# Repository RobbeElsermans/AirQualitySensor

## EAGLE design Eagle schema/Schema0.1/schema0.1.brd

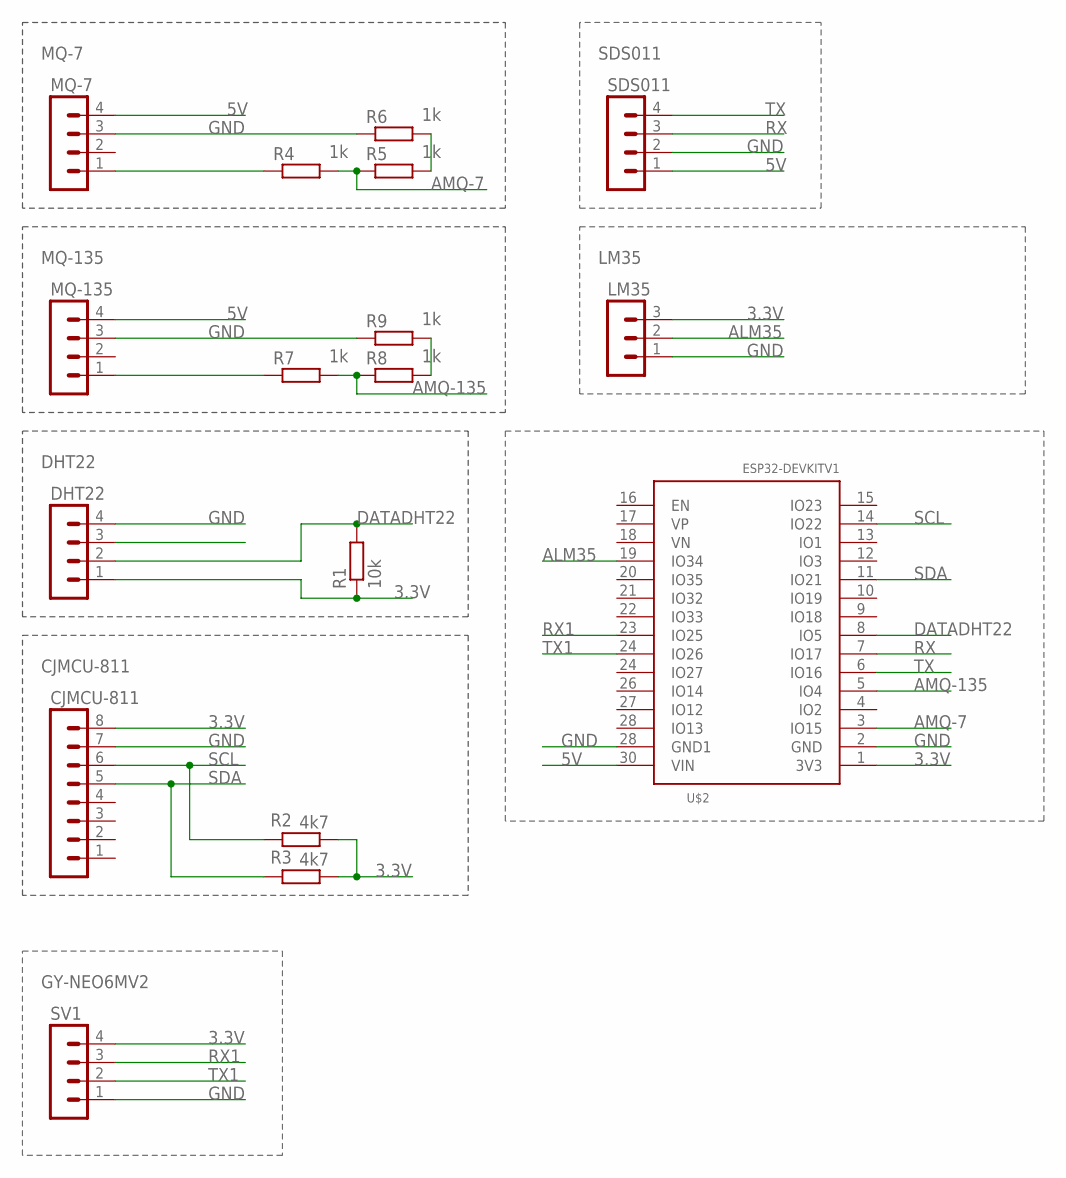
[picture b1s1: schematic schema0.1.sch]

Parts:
CJMCU-811: MA08-1
DHT22: MA04-1
LM35: MA03-1
MQ-7, MQ-135: MA04-1
R1: 10k; 0207/10
R2, R3: 4k7; 0207/10
R4, R5, R6, R7, R8, R9: 1k; 0207/10
SDS011: MA04-1
SV1: MA04-1
U$2: ESP32DEVKITV1; ESP32-DEVKITV1

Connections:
0: MQ-7.1, R4.1
1: MQ-135.1, R7.1
3.3V: CJMCU-811.8, DHT22.1, LM35.3, R1.1, R2.1, R3.1, SV1.4, U$2.1 (3V3)
5V: MQ-7.4, MQ-135.4, SDS011.1, U$2.30 (VIN)
ALM35: LM35.2, U$2.19 (IO34)
AMQ-7: R4.2, R5.1, U$2.3 (IO15)
AMQ-135: R7.2, R8.1, U$2.5 (IO4)
DATADHT22: DHT22.2, R1.2, U$2.8 (IO5)
GND: CJMCU-811.7, DHT22.4, LM35.1, MQ-7.3, MQ-135.3, R6.1, R9.1, SDS011.2, SV1.1, U$2.2 (GND), U$2.28 (IO13)
unnamed: R8.2, R9.2
unnamed: R5.2, R6.2
RX: SDS011.3, U$2.7 (IO17)
RX1: SV1.3, U$2.23 (IO25)
SCL: CJMCU-811.6, R2.2, U$2.14 (IO22)
SDA: CJMCU-811.5, R3.2, U$2.11 (IO21)
TX: SDS011.4, U$2.6 (IO16)
TX1: SV1.2, U$2.24 (IO27)

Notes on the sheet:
MQ-7
MQ-135
DHT22
CJMCU-811
SDS011
LM35
GY-NEO6MV2

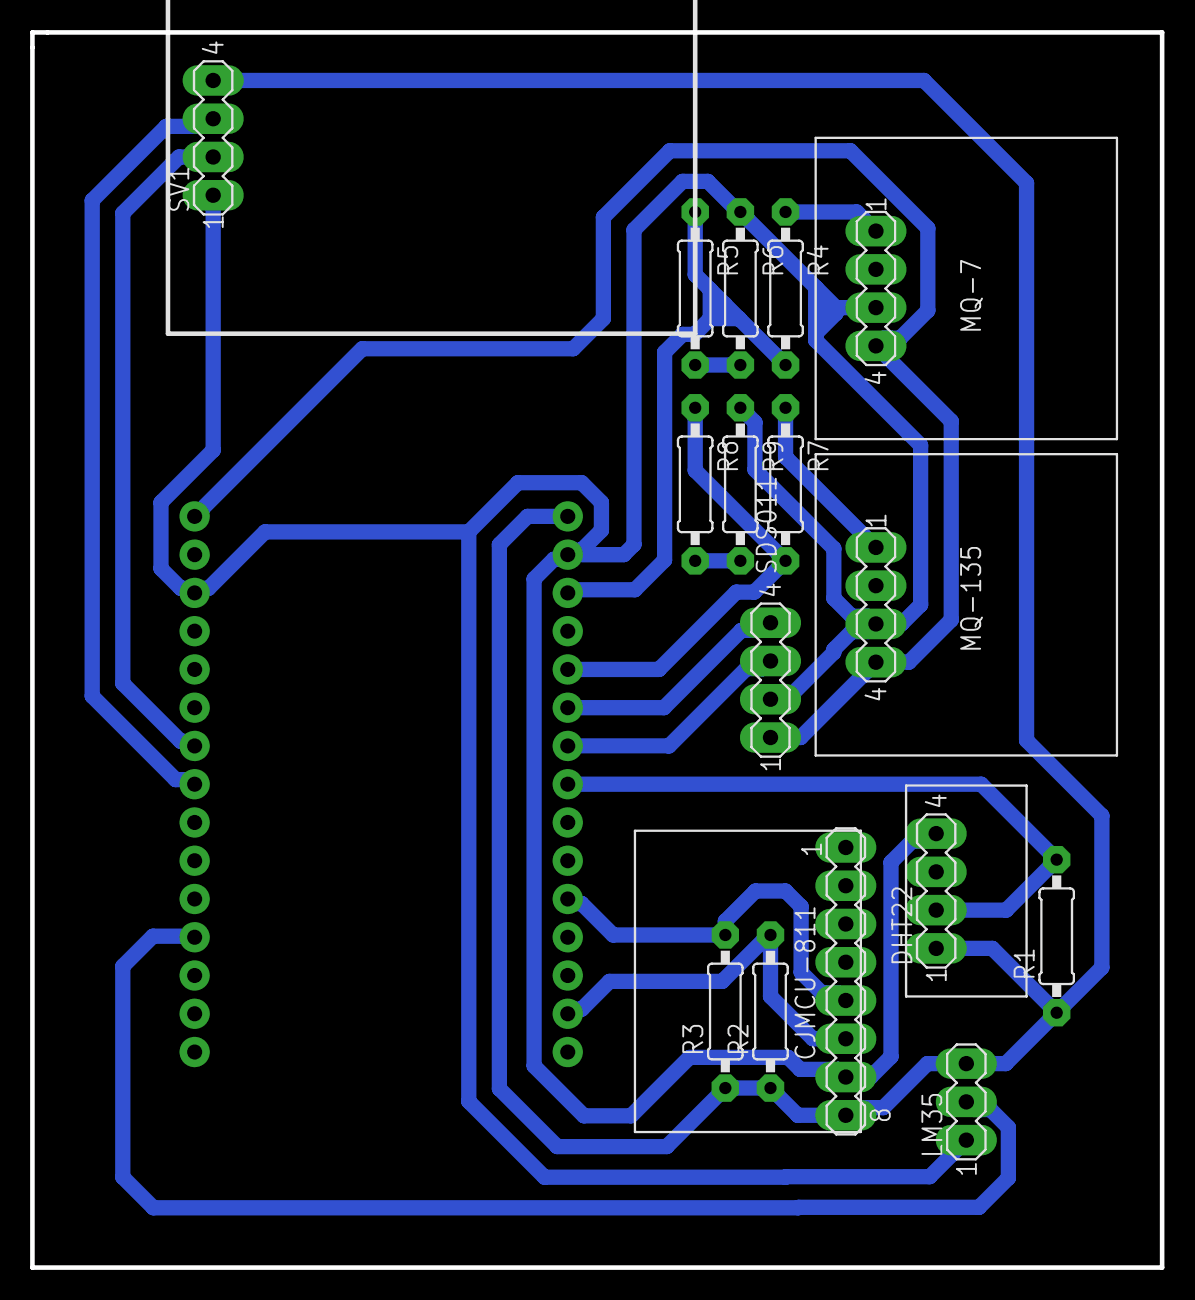
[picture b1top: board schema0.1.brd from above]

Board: 2 copper layers, 75.0 x 82.0 mm, 17 parts (1 on the bottom side), 17 nets.

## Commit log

2021-02-23 add navbar
2021-02-23 navbar bijwerken
2021-02-23 opkuis voor github page
2021-02-23 toevoeging content
2021-02-23 error fix
2021-02-24 toevoeging bronnen
2021-02-24 toevoeging hardware foto 0.2
2021-02-24 fix foto
2021-02-24 test
2021-02-24 Auto stash before rebase of "origin/main"
2021-02-24 foto fix
2021-02-24 verwijderen repo naar docs
2021-02-24 map structuur aanpassen
2021-02-24 Bronnen gesorteerd
2021-02-24 Megre confilct
2021-02-24 toevoeging onderzoek
2021-02-24 toevoeging repo
2021-02-25 Add sensor files
2021-02-25 Extra text
2021-02-26 Auto stash before checking out "HEAD"
2021-02-26 toevoeging conent
2021-02-26 aanpassen
2021-02-26 toevoeging sensoren info
2021-02-27 Picture added to software
2021-02-28 toevoeging foto en argumentatie
2021-02-28 toevoeging extra content
2021-02-28 toevoeging software analyse
2021-02-28 Spellingsfouten verbeteren
2021-02-28 blabla
2021-02-28 toevoeging Node-red
2021-02-28 toevoeging datasheet, library links
